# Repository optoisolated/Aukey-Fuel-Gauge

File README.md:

# AukeyFuelGauge

The Aukey Fuel Gauge Module is a addon for the Aukey . This design is based on the LM3914 Dot-Bar display driver.

https://www.gadgets4geeks.com.au/aukey-12000mah-external-battery-quick-charge-power-bank

The design will allow it to fit inside the battery pack with some slight modifications.

## Getting Started

### Prerequisites

### Installing

## Built With

* Kicad v5.1

## Contributing

N/a

## Versioning

N/a

## Authors

* **Optoisolated** - *Initial work* - [Optoisolated](https://github.com/Optoisolated)

See also the list of [contributors](https://github.com/optoisolated/AukeyFuelGauge/contributors) who participated in this project.

## License

This project is closed license - see the [LICENSE.md](LICENSE.md) file for details

## Acknowledgments
* LM3914 is amazing!

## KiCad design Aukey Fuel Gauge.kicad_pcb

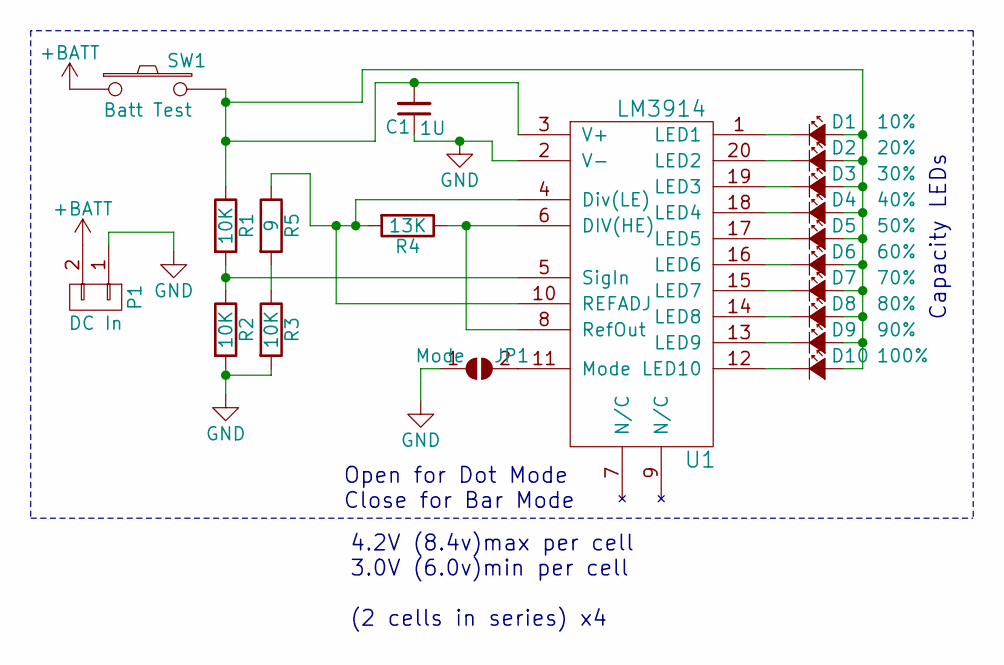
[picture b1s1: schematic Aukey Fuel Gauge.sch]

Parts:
C1: 1U; c_0603
D1: 10%; LED_0603
D2: 20%; LED_0603
D3: 30%; LED_0603
D4: 40%; LED_0603
D5: 50%; LED_0603
D6: 60%; LED_0603
D7: 70%; LED_0603
D8: 80%; LED_0603
D9: 90%; LED_0603
D10: 100%; LED_0603
JP1: Mode
P1: DC In; CONN_2.54mm_1x2
R1, R2, R3: 10K; R_0603
R4: 13K; R_0603
R5: 9; R_0603
SW1: Batt Test; smd_push
U1: LM3914; PLCC20

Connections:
+BATT: P1.2, SW1.1
GND: C1.1, JP1.1 (A), P1.1, R2.2, R3.2, U1.2 (V-)
unnamed: C1.2, D1.2 (A), D2.2 (A), D3.2 (A), D4.2 (A), D5.2 (A), D6.2 (A), D7.2 (A), D8.2 (A), D9.2 (A), D10.2 (A), R1.1, SW1.2, U1.3 (V+)
unnamed: D1.1 (K), U1.1 (LED1)
unnamed: D2.1 (K), U1.20 (LED2)
unnamed: D3.1 (K), U1.19 (LED3)
unnamed: D4.1 (K), U1.18 (LED4)
unnamed: D5.1 (K), U1.17 (LED5)
unnamed: D6.1 (K), U1.16 (LED6)
unnamed: D7.1 (K), U1.15 (LED7)
unnamed: D8.1 (K), U1.14 (LED8)
unnamed: D9.1 (K), U1.13 (LED9)
unnamed: D10.1 (K), U1.12 (LED10)
unnamed: JP1.2 (B), U1.11 (Mode)
unnamed: R1.2, R2.1, U1.5 (SigIn)
unnamed: R3.1, R5.2
unnamed: R4.1, U1.6 (DIV(HE)), U1.8 (RefOut)
unnamed: R4.2, R5.1, U1.4 (Div(LE)), U1.10 (REFADJ)

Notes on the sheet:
4.2V (8.4v)max per cell 3.0V (6.0v)min per cell (2 cells in series) x4
Open for Dot Mode Close for Bar Mode
Capacity LEDs

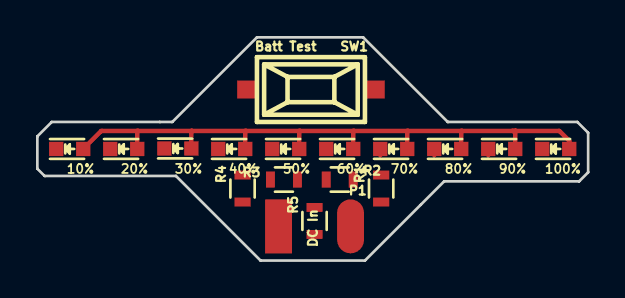
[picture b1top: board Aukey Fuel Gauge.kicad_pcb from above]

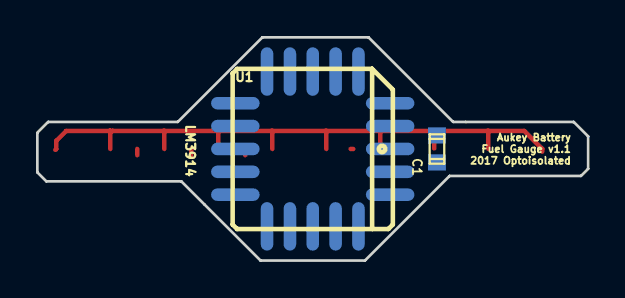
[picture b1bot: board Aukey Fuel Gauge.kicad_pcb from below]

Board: 2 copper layers, 30.6 x 12.4 mm, 19 parts (2 on the bottom side), 17 nets.

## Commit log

2019-04-20 Initial commit
    Added Solder Jumper into schematic for Mode selection. Schematic is done. PCB Layout is laid out but still needs traces run and part designed for Jumper.
2019-04-20 Delete sym-lib-table
    Extra file. Not needed.
